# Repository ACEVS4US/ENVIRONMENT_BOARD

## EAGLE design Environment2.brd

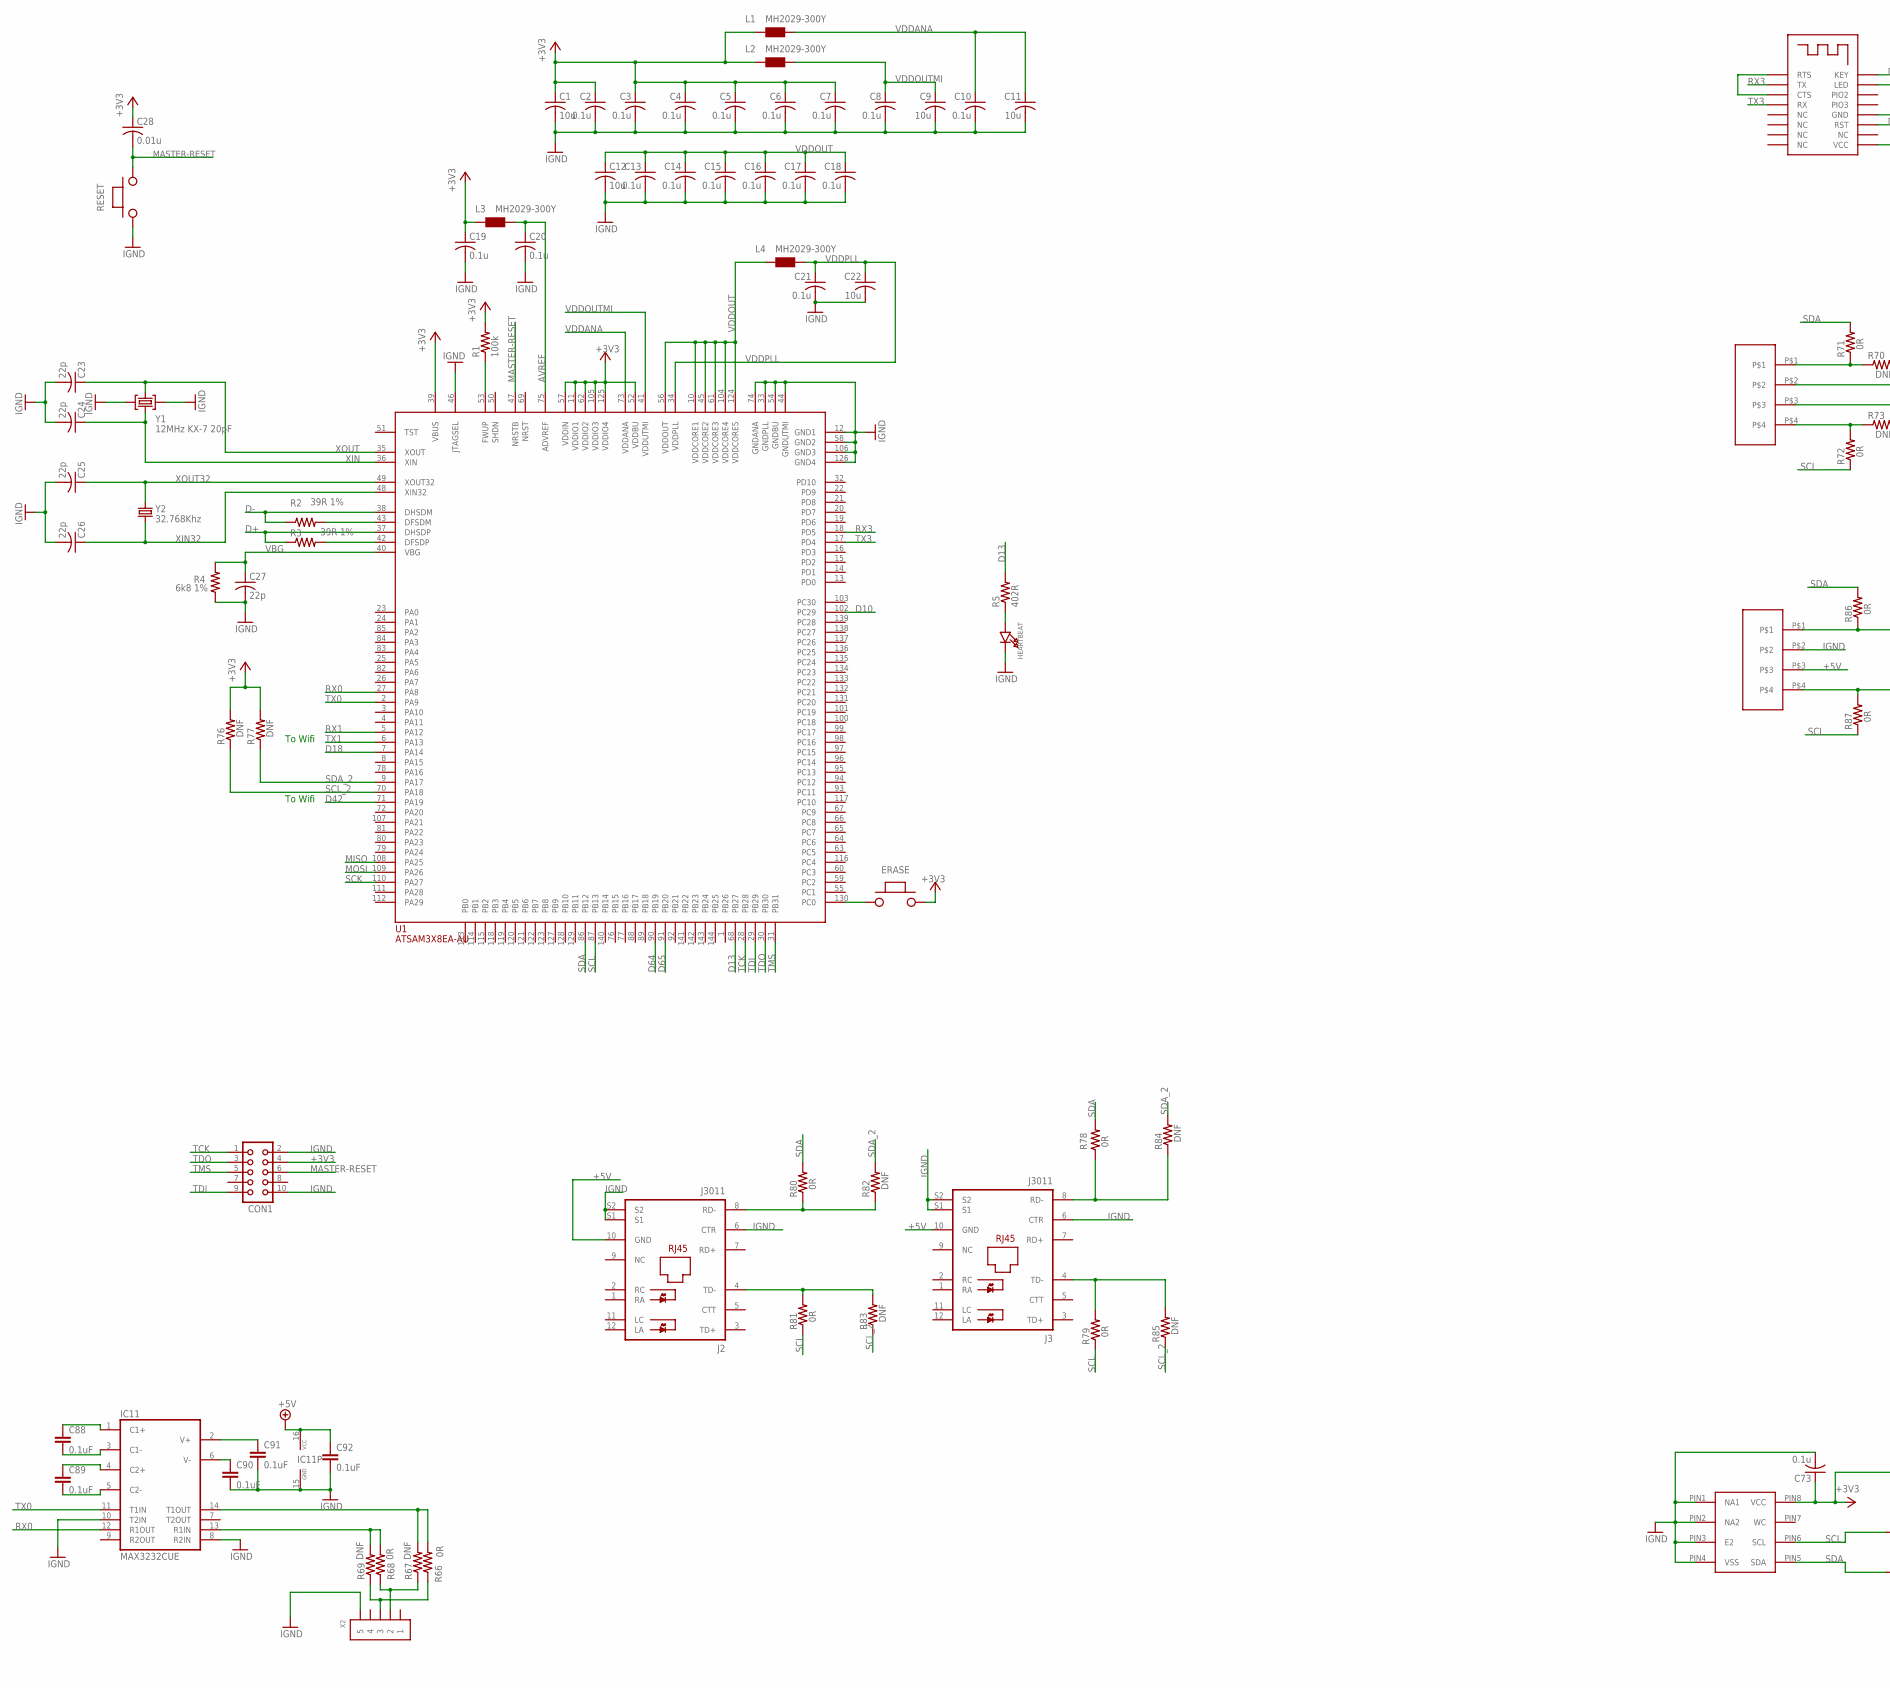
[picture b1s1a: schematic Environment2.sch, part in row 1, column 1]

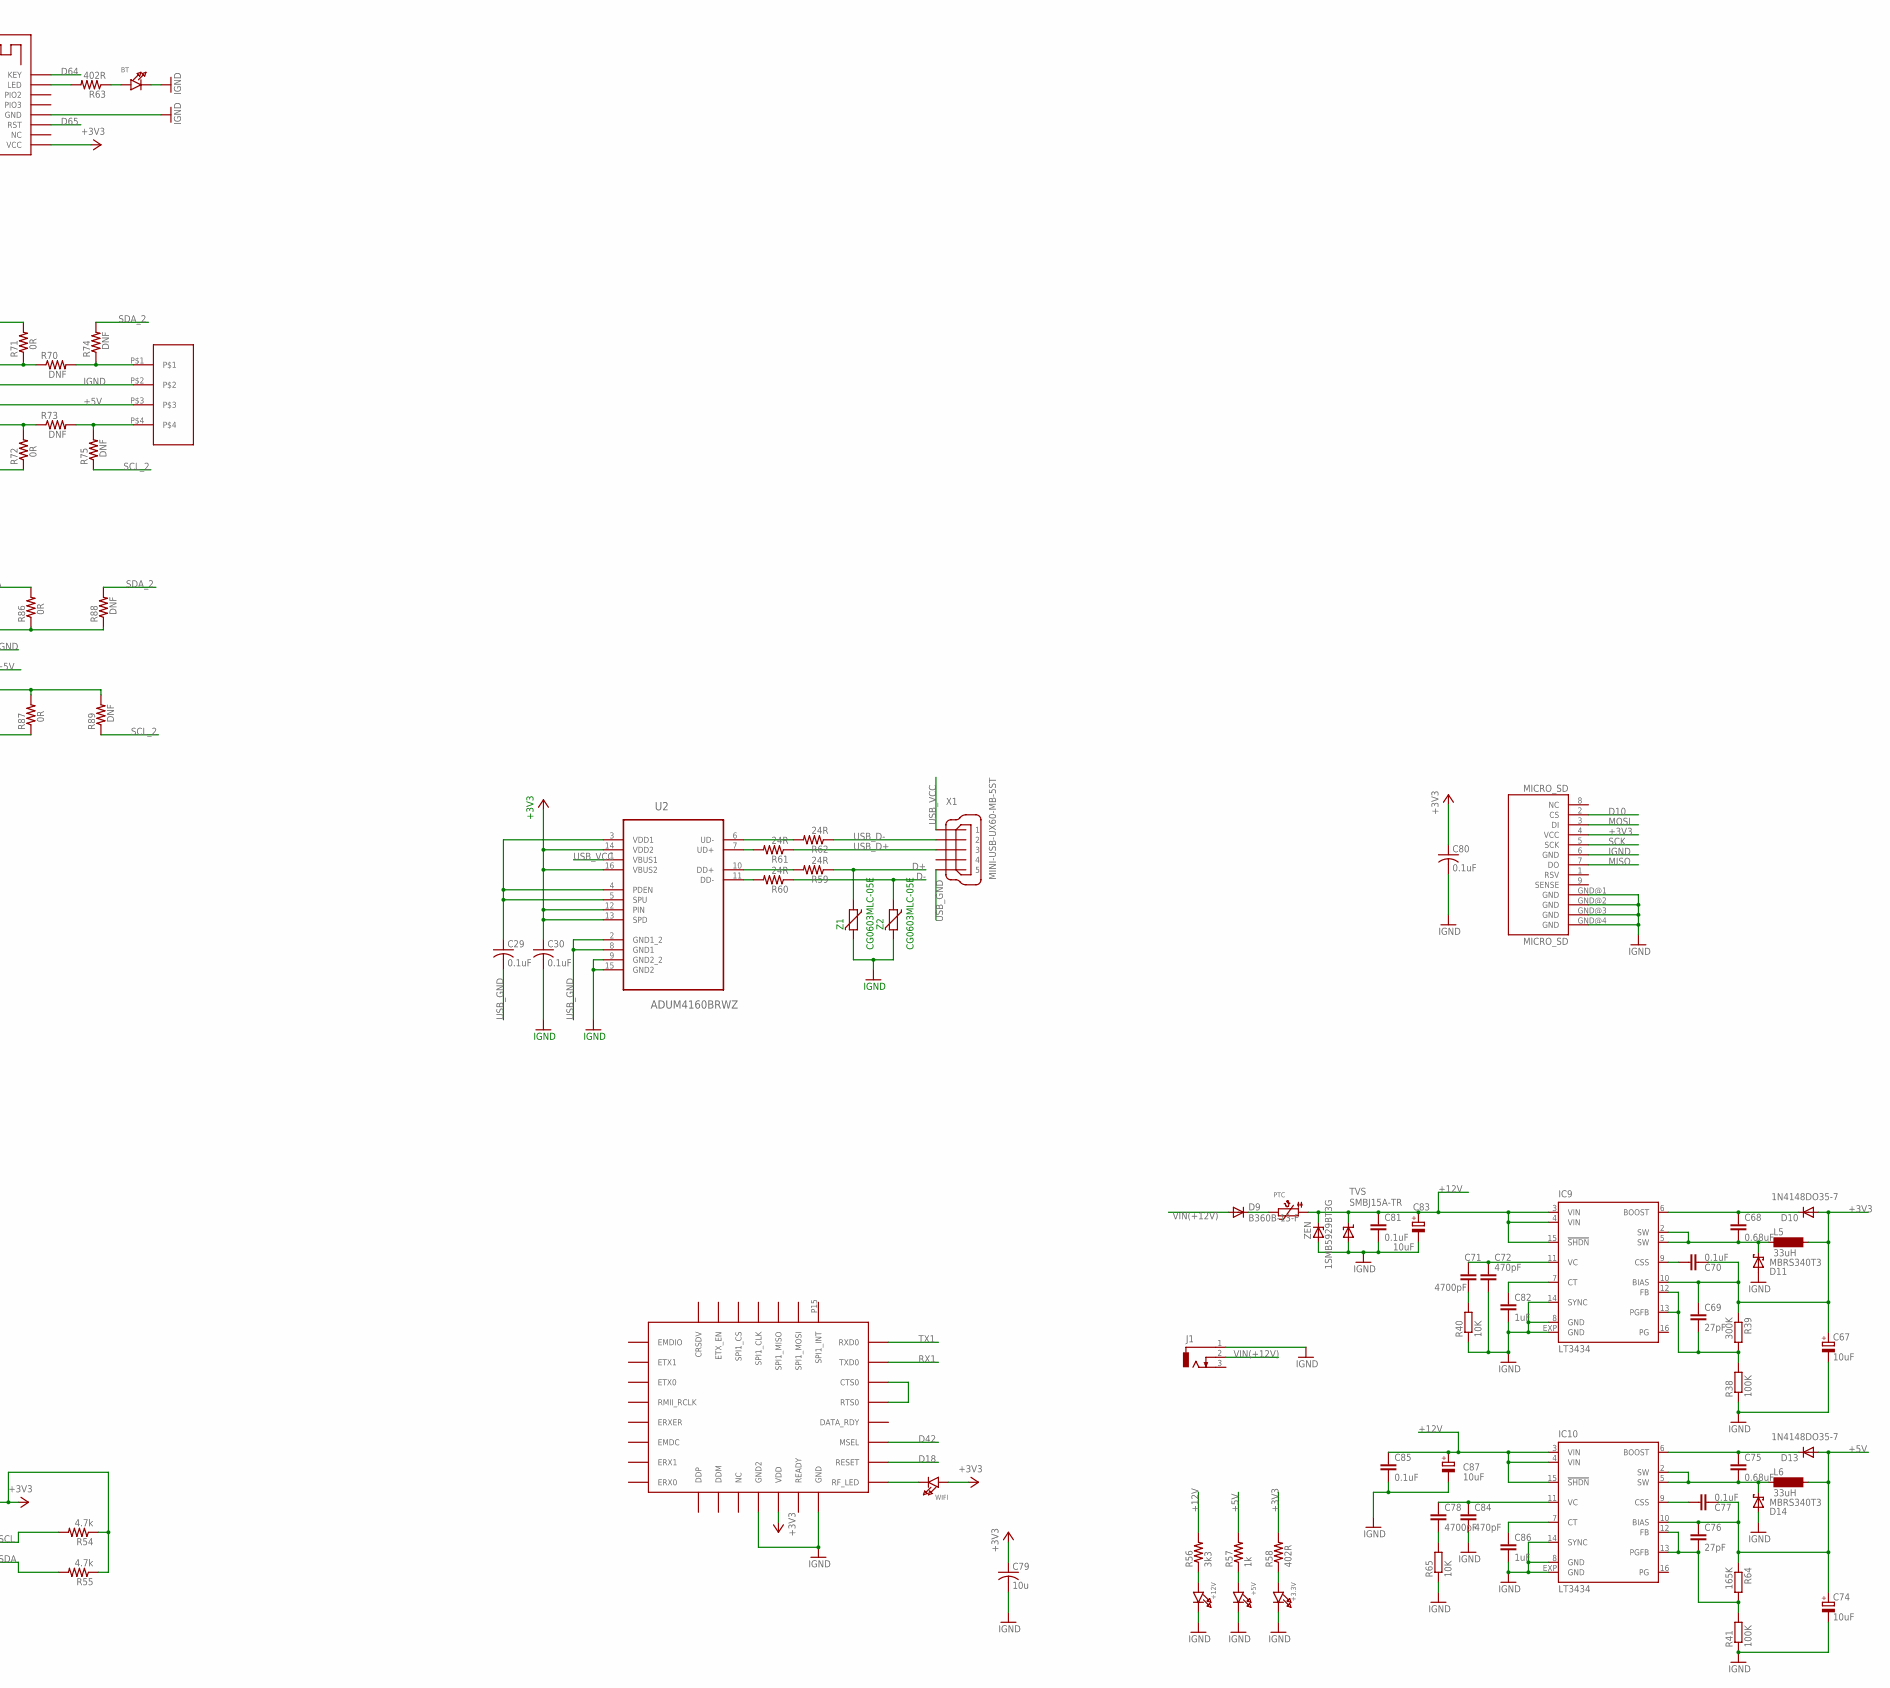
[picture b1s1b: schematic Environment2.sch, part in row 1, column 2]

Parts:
+3.3V, +5V, +12V: LED0805; CHIPLED_0805
BT: LED0805; CHIPLED_0805
C1, C9, C11, C12, C22, C79: 10u; C0805
C2, C3, C4, C5, C6, C7, C8, C10, C13, C14, C15, C16, C17, C18, C19, C20, C21, C73: 0.1u; C0805
C23, C24: 22p; C1206
C25, C26, C27: 22p; C0805
C28: 0.01u; C0805
C29, C30, C80: 0.1uF; C0805
C67, C74, C83, C87: 10uF; SMC_D
C68, C75: 0.68uF; C0603
C69, C76: 27pF; C0603
C70, C77, C81, C85, C88, C89, C90, C91, C92: 0.1uF; C0603
C71, C78: 4700pF; C0603
C72, C84: 470pF; C0603
C82, C86: 1uF; C0603
CON1: CON10
D9: B360B-13-F; SMB
D10, D13: 1N4148DO35-7; DO35-7
D11, D14: MBRS340T3; SMC
ERASE: PUCHBUTTON
HEARTBEAT: LED0805; CHIPLED_0805
IC9, IC10: LT3434; TSSOP16EXP
IC11: MAX3232CUE; TSSOP16
J1: DCJ0303
J2, J3: J3011; J30
L1, L2, L3, L4: MH2029-300Y; 0805
L5, L6: 33uH; MS85
MICRO_SD: MICRO_SD; MICROSD_PP
PTC: PTC1812
R1: 100k; R0805
R2, R3: 39R 1%; R0805
R4: 6k8 1%; R0805
R5, R58, R63: 402R; R0805
R38, R41: 100K; R0603
R39: 300K; R0603
R40, R65: 10K; R0603
R54, R55: 4.7k; R0805
R56: 3k3; R0805
R57: 1k; R0805
R59, R60, R61, R62: 24R; R0805
R64: 165K; R0603
R66, R68, R71, R72, R78, R79, R80, R81, R86, R87: 0R; R0805
R67, R69, R70, R73, R74, R75, R76, R77, R82, R83, R84, R85, R88, R89: DNF; R0805
RESET: PUCHBUTTON
TVS: SMBJ15A-TR; SMBJ
U1: ATSAM3X8EA-AU; LQFP144
U2: ADUM4160BRWZ; SOIC127P1032X265-16N
U7: CK_CUSTOM_M24M02-DRMN6TP; CK_CUSTOM_SOIC8
U8, U9, U10: 560020-04; 560020-4
U$1: NANOREACH
U$3: HM-13
WIFI: LED0805; CHIPLED_0805
X1: MINI-USB-UX60-MB-5ST; UX60-MB-5ST
X2: CONN_5-1-502386; CM-502386-05
Y1: 12MHz KX-7 20pF; CRYSTAL-3.2-2.5
Y2: 32.768Khz; ARDUINO_WIFI_SHIELD_V018_TG_RESONATOR_EPSON_FC_145
Z1, Z2: CG0603MLC-05E; CT/CN0603
ZEN: 1SMB5929BT3G; SMB

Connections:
+3V3: C1.1, C2.1, C3.1, C4.1, C5.1, C6.1, C7.1, C19.1, C28.1, C30.1, C67.+, C69.1, C70.2, C73.1, C79.1, C80.1, CON1.4, D10.A, ERASE.P$2, IC9.10 (BIAS), L1.1, L2.1, L3.1, L5.2, MICRO_SD.4 (VCC), R1.2, R39.1, R54.1, R55.1, R58.2, R76.2, R77.2, U1.11 (VDDIO1), U1.39 (VBUS), U1.52 (VDDBU), U1.57 (VDDIN), U1.62 (VDDIO2), U1.105 (VDDIO3), U1.125 (VDDIO4), U2.12 (PIN), U2.13 (SPD), U2.14 (VDD2), U2.16 (VBUS2), U7.PIN8 (VCC), U$1.P1 (VDD), U$3.P$9 (VCC), WIFI.A
+5V: C74.+, C76.1, C77.2, C92.1, D13.A, IC10.10 (BIAS), IC11.16 (VCC), J2.10 (GND), L6.2, R57.2, R64.1, U8.P$3, U9.P$3, U10.P$3
+12V: C81.1, C83.+, C85.1, C87.+, IC9.3 (VIN), IC9.4 (VIN), IC9.15 (!SHDN), IC10.3 (VIN), IC10.4 (VIN), IC10.15 (!SHDN), PTC.P$1 (1), R56.2, TVS.C, ZEN.C
A: R70.2, R74.1, U9.P$1
AVREF: C20.1, L3.2, U1.75 (ADVREF)
B: R73.2, R75.2, U9.P$4
D10: MICRO_SD.2 (CS), U1.102 (PC29)
D13: R5.2, U1.68 (PB27)
D18: U1.7 (PA14), U$1.P9 (RESET)
D42: U1.71 (PA19), U$1.P8 (MSEL)
D64: U1.90 (PB19), U$3.P$16 (KEY)
D65: U1.91 (PB20), U$3.P$11 (RST)
D+: R3.1, R59.1, U1.37 (DHSDP), Z1.1
D-: R2.1, R60.1, U1.38 (DHSDM), Z2.1
ERASE_S: ERASE.P$1, U1.130 (PC0)
IGND: +3.3V.C, +5V.C, +12V.C, BT.C, C1.2, C2.2, C3.2, C4.2, C5.2, C6.2, C7.2, C8.2, C9.2, C10.2, C11.2, C12.2, C13.2, C14.2, C15.2, C16.2, C17.2, C18.2, C19.2, C20.2, C21.2, C22.2, C23.2, C24.2, C25.2, C26.2, C27.2, C30.2, C67.-, C72.2, C73.2, C74.-, C79.2, C80.2, C81.2, C82.2, C83.-, C84.2, C85.2, C86.2, C87.-, C90.2, C91.2, C92.2, CON1.2, CON1.10, D11.A, D14.A, HEARTBEAT.C, IC9.8 (GND), IC9.14 (SYNC), IC9.EXP (GND), IC10.8 (GND), IC10.14 (SYNC), IC10.EXP (GND), IC11.8 (R2IN), IC11.10 (T2IN), IC11.15 (GND), J1.1, J2.6 (CTR), J2.S1, J2.S2, J3.6 (CTR), J3.S1, J3.S2, MICRO_SD.6 (GND), MICRO_SD.GND@1 (GND), MICRO_SD.GND@2 (GND), MICRO_SD.GND@3 (GND), MICRO_SD.GND@4 (GND), R4.1, R38.1, R40.1, R41.1, R65.1, RESET.P$1, TVS.A, U1.12 (GND1), U1.33 (GNDPLL), U1.44 (GNDUTMI), U1.46 (JTAGSEL), U1.54 (GNDBU), U1.58 (GND2), U1.74 (GNDANA), U1.106 (GND3), U1.126 (GND4), U2.9 (GND2_2), U2.15 (GND2), U7.PIN1 (NA1), U7.PIN2 (NA2), U7.PIN3 (E2), U7.PIN4 (VSS), U8.P$2, U9.P$2, U10.P$2, U$1.P2 (GND), U$1.P20 (GND2), U$3.P$12 (GND), X2.5, Y1.2 (GND), Y1.4 (GND), Z1.2, Z2.2, ZEN.A
MASTER-RESET: C28.2, CON1.6, RESET.P$2, U1.47 (NRSTB)
MISO: MICRO_SD.7 (DO), U1.108 (PA25)
MOSI: MICRO_SD.3 (DI), U1.109 (PA26)
unnamed: +3.3V.A, R58.1
unnamed: D9.C, PTC.P$2 (2)
unnamed: +5V.A, R57.1
unnamed: C29.1, U2.3 (VDD1), U2.4 (PDEN), U2.5 (SPU)
unnamed: HEARTBEAT.A, R5.1
unnamed: U$3.P$1 (RTS), U$3.P$3 (CTS)
unnamed: R62.2, U2.6 (UD-)
unnamed: R61.2, U2.7 (UD+)
unnamed: C71.1, C72.1, IC9.11 (VC)
unnamed: C70.1, IC9.9 (CSS)
unnamed: C68.1, D10.C, IC9.6 (BOOST)
unnamed: C71.2, R40.2
unnamed: C68.2, D11.C, IC9.2 (SW), IC9.5 (SW), L5.1
unnamed: C82.1, IC9.7 (CT)
unnamed: R59.2, U2.10 (DD+)
unnamed: +12V.A, R56.1
unnamed: R60.2, U2.11 (DD-)
unnamed: BT.A, R63.1
unnamed: R63.2, U$3.P$15 (LED)
unnamed: U$1.P5 (CTS0), U$1.P6 (RTS0)
unnamed: R2.2, U1.43 (DFSDM)
unnamed: R3.2, U1.42 (DFSDP)
unnamed: R1.1, U1.53 (FWUP)
unnamed: C69.2, IC9.12 (FB), IC9.13 (PGFB), R38.2, R39.2
unnamed: C75.1, D13.C, IC10.6 (BOOST)
unnamed: C77.1, IC10.9 (CSS)
unnamed: C75.2, D14.C, IC10.2 (SW), IC10.5 (SW), L6.1
unnamed: C86.1, IC10.7 (CT)
unnamed: C78.1, C84.1, IC10.11 (VC)
unnamed: C78.2, R65.2
unnamed: C88.1, IC11.1 (C1+)
unnamed: C88.2, IC11.3 (C1-)
unnamed: C89.1, IC11.4 (C2+)
unnamed: R66.1, R69.1, X2.3
unnamed: R67.1, R68.1, X2.2
unnamed: R70.1, R71.1, U10.P$1
unnamed: R72.2, R73.1, U10.P$4
unnamed: J2.8 (RD-), R80.1, R82.1
unnamed: J2.4 (TD-), R81.2, R83.2
unnamed: J3.8 (RD-), R78.1, R84.1
unnamed: J3.4 (TD-), R79.2, R85.2
unnamed: R86.1, R88.1, U8.P$1
unnamed: R87.2, R89.2, U8.P$4
unnamed: C76.2, IC10.12 (FB), IC10.13 (PGFB), R41.2, R64.2
unnamed: C89.2, IC11.5 (C2-)
unnamed: C90.1, IC11.6 (V-)
unnamed: IC11.14 (T1OUT), R66.2, R67.2
unnamed: IC11.13 (R1IN), R68.2, R69.2
unnamed: C91.1, IC11.2 (V+)
RX0: IC11.12 (R1OUT), U1.27 (PA8)
RX1: U1.5 (PA12), U$1.P4 (TXD0)
RX3: U1.18 (PD5), U$3.P$2 (TX)
SCK: MICRO_SD.5 (SCK), U1.110 (PA27)
SCL: R54.2, R72.1, R79.1, R81.1, R87.1, U1.87 (PB13), U7.PIN6 (SCL)
SCL_2: R75.1, R76.1, R83.1, R85.1, R89.1, U1.70 (PA18)
SDA: R55.2, R71.2, R78.2, R80.2, R86.2, U1.86 (PB12), U7.PIN5 (SDA)
SDA_2: R74.2, R77.1, R82.2, R84.2, R88.2, U1.9 (PA17)
TCK: CON1.1, U1.28 (PB28)
TDI: CON1.9, U1.29 (PB29)
TDO: CON1.3, U1.30 (PB30)
TMS: CON1.5, U1.31 (PB31)
TX0: IC11.11 (T1IN), U1.2 (PA9)
TX1: U1.6 (PA13), U$1.P3 (RXD0)
TX3: U1.17 (PD4), U$3.P$4 (RX)
USB_D+: R61.1, X1.3
USB_D-: R62.1, X1.2
USB_GND: C29.2, U2.2 (GND1_2), U2.8 (GND1), X1.5
USB_VCC: U2.1 (VBUS1), X1.1
VBG: C27.1, R4.2, U1.40 (VBG)
VDDANA: C10.1, C11.1, L1.2, U1.73 (VDDANA)
VDDOUT: C12.1, C13.1, C14.1, C15.1, C16.1, C17.1, C18.1, L4.1, U1.10 (VDDCORE1), U1.45 (VDDCORE2), U1.56 (VDDOUT), U1.61 (VDDCORE3), U1.104 (VDDCORE4), U1.124 (VDDCORE5)
VDDOUTMI: C8.1, C9.1, L2.2, U1.41 (VDDUTMI)
VDDPLL: C21.1, C22.1, L4.2, U1.34 (VDDPLL)
VIN(+12V): D9.A, J1.2
WIFI: U$1.P10 (RF_LED), WIFI.C
XIN: C24.1, U1.36 (XIN), Y1.1 (C1)
XIN32: C26.1, U1.48 (XIN32), Y2.P$2 (2)
XOUT: C23.1, U1.35 (XOUT), Y1.3 (C2)
XOUT32: C25.1, U1.49 (XOUT32), Y2.P$1 (1)

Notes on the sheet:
To Wifi

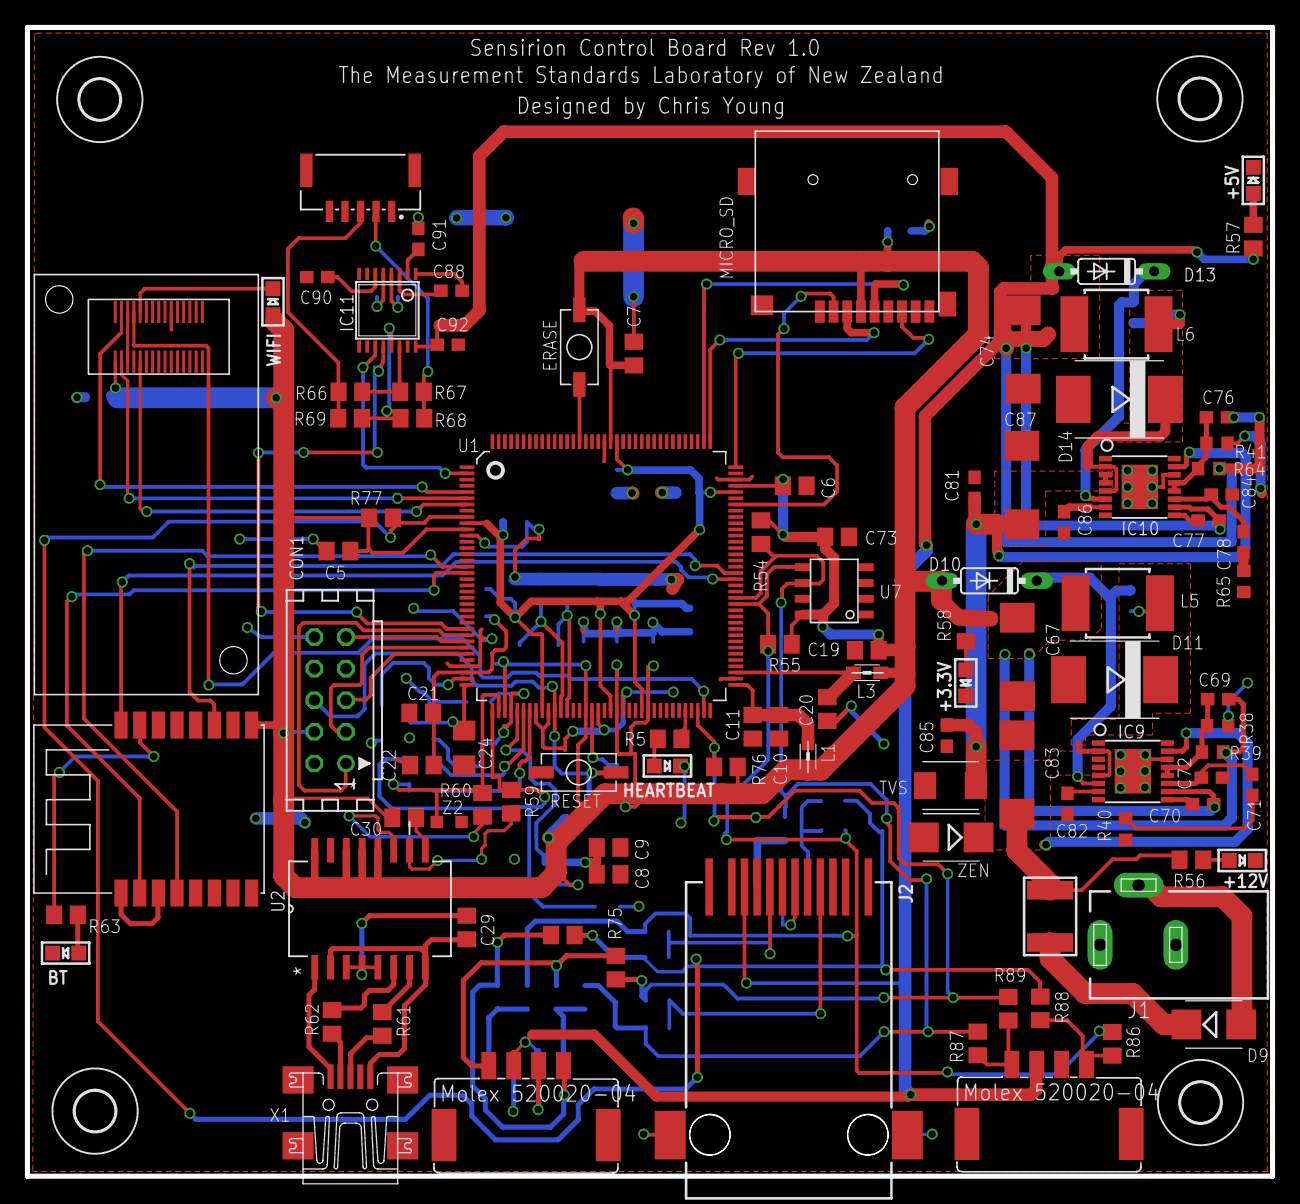
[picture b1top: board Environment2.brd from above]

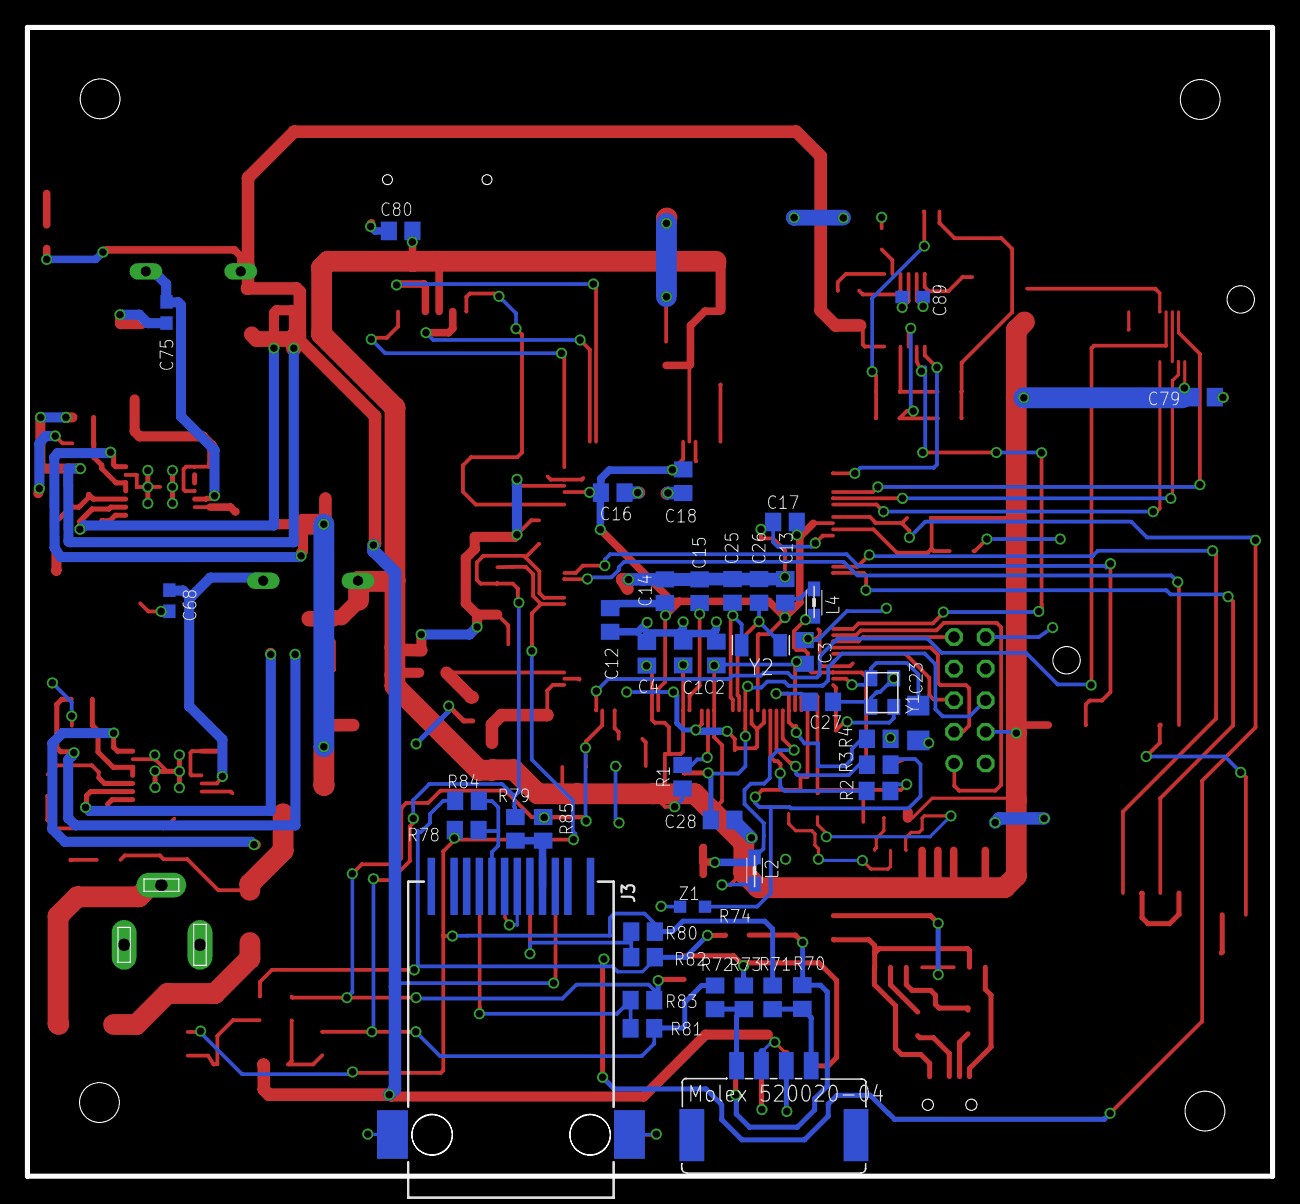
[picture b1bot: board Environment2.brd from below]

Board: 2 copper layers, 100.1 x 92.3 mm, 149 parts (44 on the bottom side), 98 nets.

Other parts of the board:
U$2, U$4, U$5, U$6: 3,2

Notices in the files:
parts and their libraries:
microbuilder: This work is placed in the public domain, and may be freely used for commercial and non-commercial work with the following conditions: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
pulse-eng: Copyright (C) 2008, Bob Starr
